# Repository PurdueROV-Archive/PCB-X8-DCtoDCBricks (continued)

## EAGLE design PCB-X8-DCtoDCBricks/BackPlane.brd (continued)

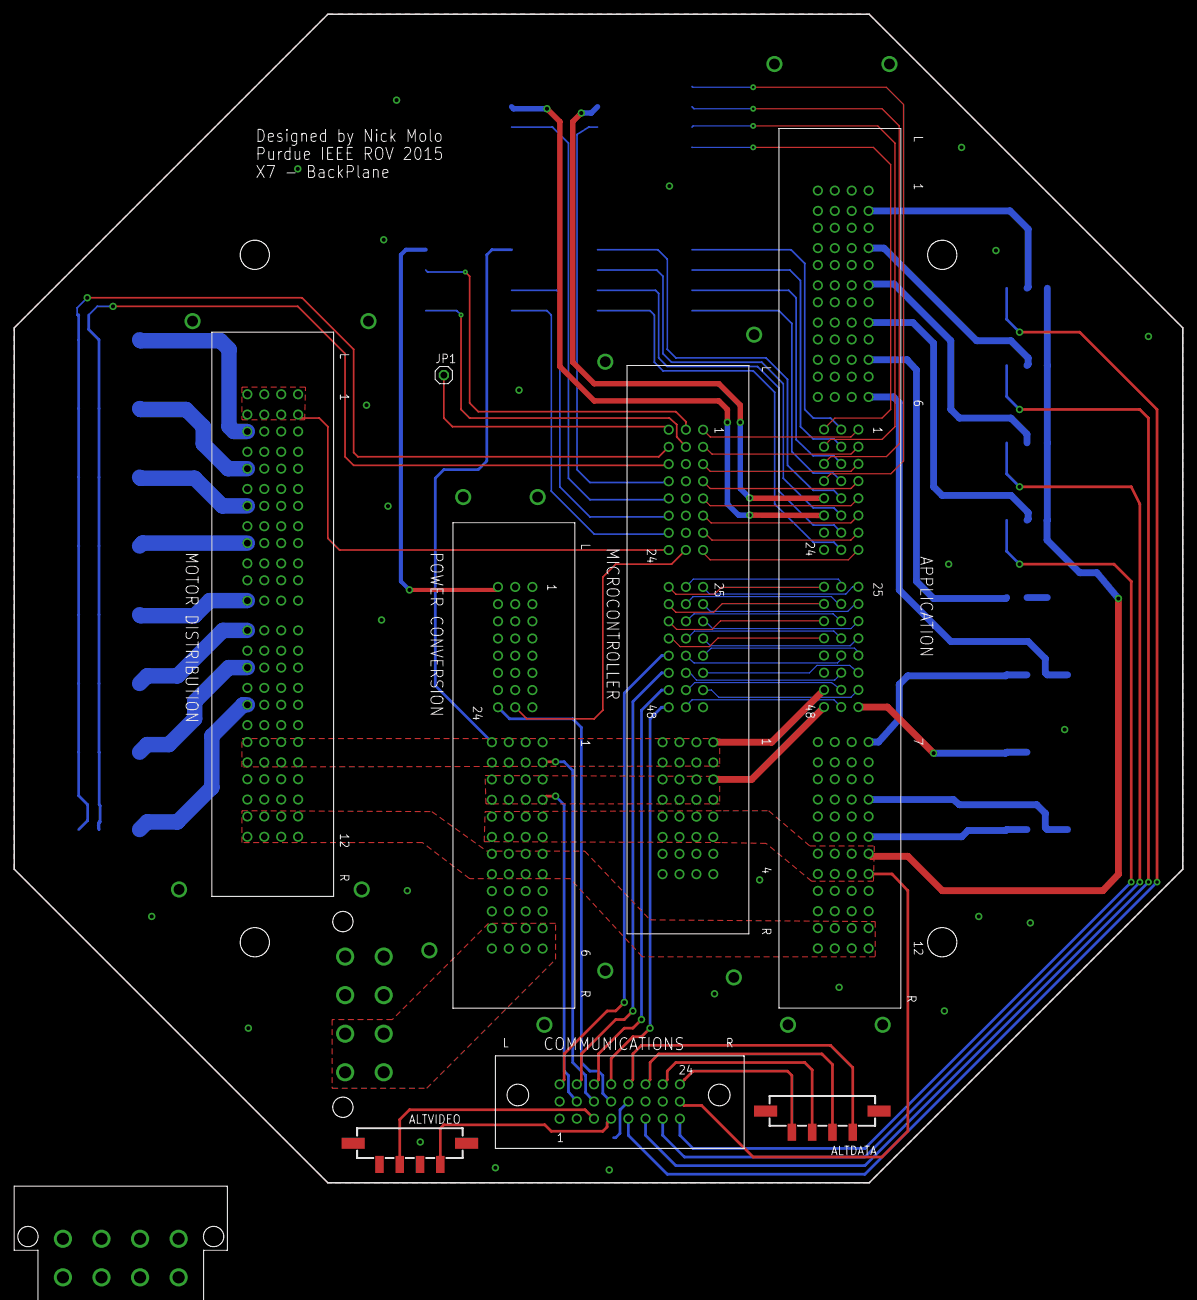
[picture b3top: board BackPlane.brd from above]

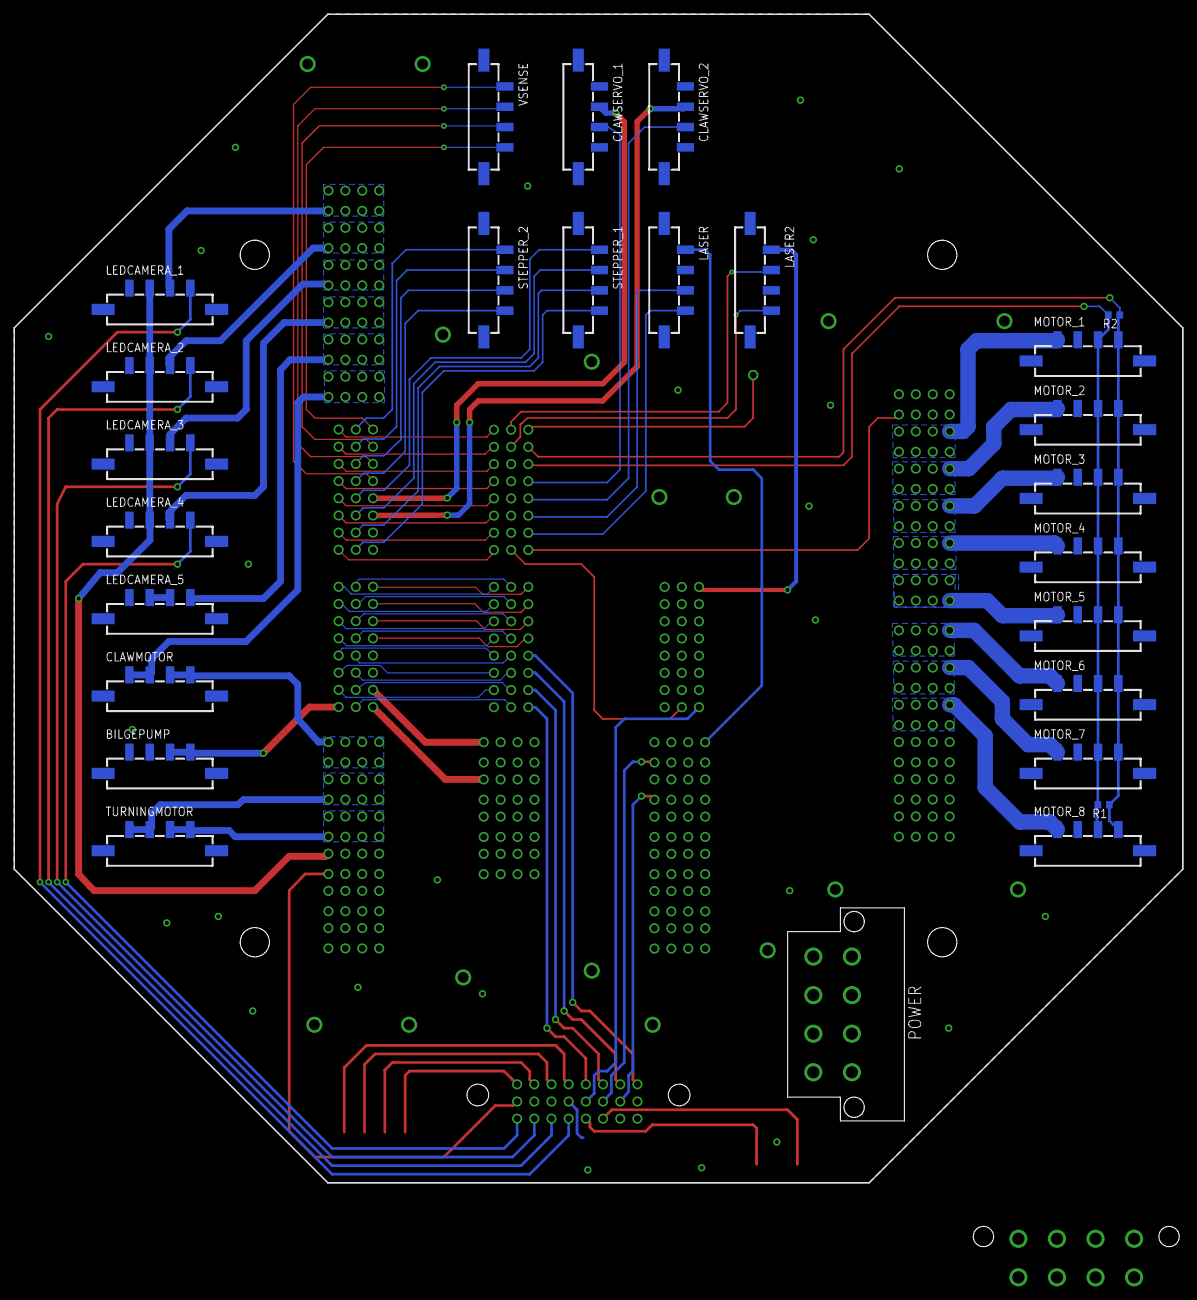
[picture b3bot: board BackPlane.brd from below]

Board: 2 copper layers, 172.7 x 172.7 mm, 35 parts (26 on the bottom side), 93 nets.

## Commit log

2015-11-12 boards have been added
    see above
2015-11-17 Revert "boards have been added"
    This reverts commit 7648aec1737d14e43d6219970dc1d9d46a4b2c61.
2015-11-18 updated brick board to new half brick
2015-11-21 addressing and labels
2015-11-21 added LEDs to smbalert and pg
2015-11-21 changed PGND to GND
2015-11-25 got rid of old capacitors and added connectors
2015-11-25 new layout
2015-12-01 added 48V connector
2015-12-04 four pin connectors
2015-12-05 power connectors, board layout basic
2015-12-05 fixed messy capacitors
2015-12-05 Added Updated Connector
2015-12-05 stole current sensor, 12-5V
    yo ho ho
2015-12-05 Updated schematic to look nice
2015-12-05 temporary placement of power bricks and conectors
2015-12-09 switched from 5V buck converter to linear converter
2015-12-09 added 3 other bricks/improved layout
2015-12-10 added Bayley's cool new 4 connector micro
2015-12-10 no current sensor
2015-12-12 improved layout
2015-12-16 placing parts1
2015-12-20 added polygons
    Added polygons for 12V signals and for gnds
2015-12-23 drew traces for PWM, SDA, and SCL in lower right corner
2015-12-27 Fixed up microcontroller section of board
2015-12-28 More progress on the microcontroller circuit
2015-12-28 Done with the microcontroller for the power bricks board
2015-12-28 finished: PWM, wip: SDA, SCL traces
2015-12-28 finished: PWM, SDA, SCL
    need to fix right angles
2015-12-28 fixed PWM, SDA, SCL traces and right angle junctions
2015-12-30 Completed more traces
2015-12-30 top GND plane and clean up
    Added top ground plane, cleaned up messy signals and other mistakes
2015-12-30 getting rid of extras
2015-12-30 changed pwm signal to thrusters
2015-12-31 sizing and aesthetic changes
2015-12-31 Fixed design rule errors
2016-01-01 overlap fixes
    vias still have clearance issues
2016-01-02 Changed pins for i2c
2016-01-03 Added GND vias around the board
2016-01-03 Replaced the stm32f405 chip with a corrected version
2016-01-06 drc error fixes
2016-01-06 SCL and SDA test vias
2016-01-06 many aesthetic corrections
2016-01-07 clearance error fix
    restring pad values (top, inner, bottom) changed to 0% from 25%
2016-01-08 clearance made for Advanced Circuits
    adjusted DRC restring pad (top,bottom,inner) values from 10mil to 9mil
2016-01-08 silkscreen cleanup
2016-01-08 more silkscreen
2016-01-08 Silkscreen 3: the Silkening
2016-01-08 Silkscreen 4: The Silkquel (and a few)
2016-01-09 Silkscreens of the Caribbean 3: At Board's End
    actually 5 but whatever
2016-01-09 gerbers generated, compressed
2016-01-10 Added header pins for debugging
2016-01-11 updated johnny depp
2016-01-11 updated gerbers
2016-01-11 refixed restring options, redrew curvy trace
2016-01-11 updated gerbers to reflect no errors
    how do you pronounce gerbers
2016-01-13 Cleaned up the board layout
2016-01-16 moved sda/scl pins and header pins
2016-01-16 more little fixes
2016-01-16 final drcing
2016-01-16 added screw holes
2016-01-16 fixed drc, again
2016-01-16 Final Check 1!
2016-01-16 Fixed github issues
2016-01-16 added screws, moved led in top right (power), assured drc rules
2016-01-18 redoing fixes/re-adding bypass capacitor on can
2016-01-18 gerbers!
2016-01-18 cleaning up the trace
2016-01-19 more trace fixes
2016-04-21 removed Microcontroller
    removed everything from microcontroller page of schematic EXCEPT for the
    microusb
    removed 2 data pins from microusb, planning to install Teensy 3.2
    footprint and wiring vin of teensy to vcc of micro usb, gnd to gnd
2016-04-23 added teensy footprint, pwm chip schematic
    also fixed resistor by his beard (r27)
    still need to finish wiring teensy
2016-04-23 finished wiring teensy, can
2016-04-23 cleaned up traces
2016-04-23 Removed physical i2c traces to thrusters, bricks
    also removed unnecessary pwm chip stuff
2016-04-23 misc fixes
2016-04-23 fixed cap, named boards and caps
2016-04-23 changed names of connectors, added header pins for pwm chip
2016-04-24 cleaned traces, fixed capacitor orientation
2016-04-24 replaced ~50% of molex microfit connectors
    replaced with vertical variant
2016-04-24 finished vert molex microfit connectors
    previous commit:
    *vertical variant was corrected in PCB-Libraries prior to replacement*
    fixed swapped pwm chan 2 and 0
    THRUST2 in top left corner
    PUMP (0) in next to last left corner
2016-04-24 laying out pwm chip
    also removed +5V from pump
2016-04-25 misc changes
2016-04-25 pwm chip headers wired
    need to give the bottom half more room so wires can come in
2016-04-25 expanded space for other traces to reach pwm lines
2016-04-25 reorganized pwm chip layout
2016-04-28 Added and Reworked Traces
    Added Traces mostly to the PWN and rerouted and cleaned up some other
    traces
2016-05-01 fixed a few DRC issues, added vias for pwm chans
2016-05-01 finished tracing, fixed bugs, added info, moved sparrow
2016-05-01 fixed GND vias
2016-05-01 fixed DRC errors according to GoldPhoenix and OSHPark
2016-05-01 resized capacitors with new cap footprint
2016-05-04 Fixed routing errors
2016-05-04 bugfixed DRC errors
2016-05-05 Fixed merge conflict
2016-05-06 refixed DRC errors
    100% good with Gold Phoenix now
2016-05-06 Gerbers generated
    Hi Carolyn
2016-05-11 added board outline file
    has .file extension because extension is required
